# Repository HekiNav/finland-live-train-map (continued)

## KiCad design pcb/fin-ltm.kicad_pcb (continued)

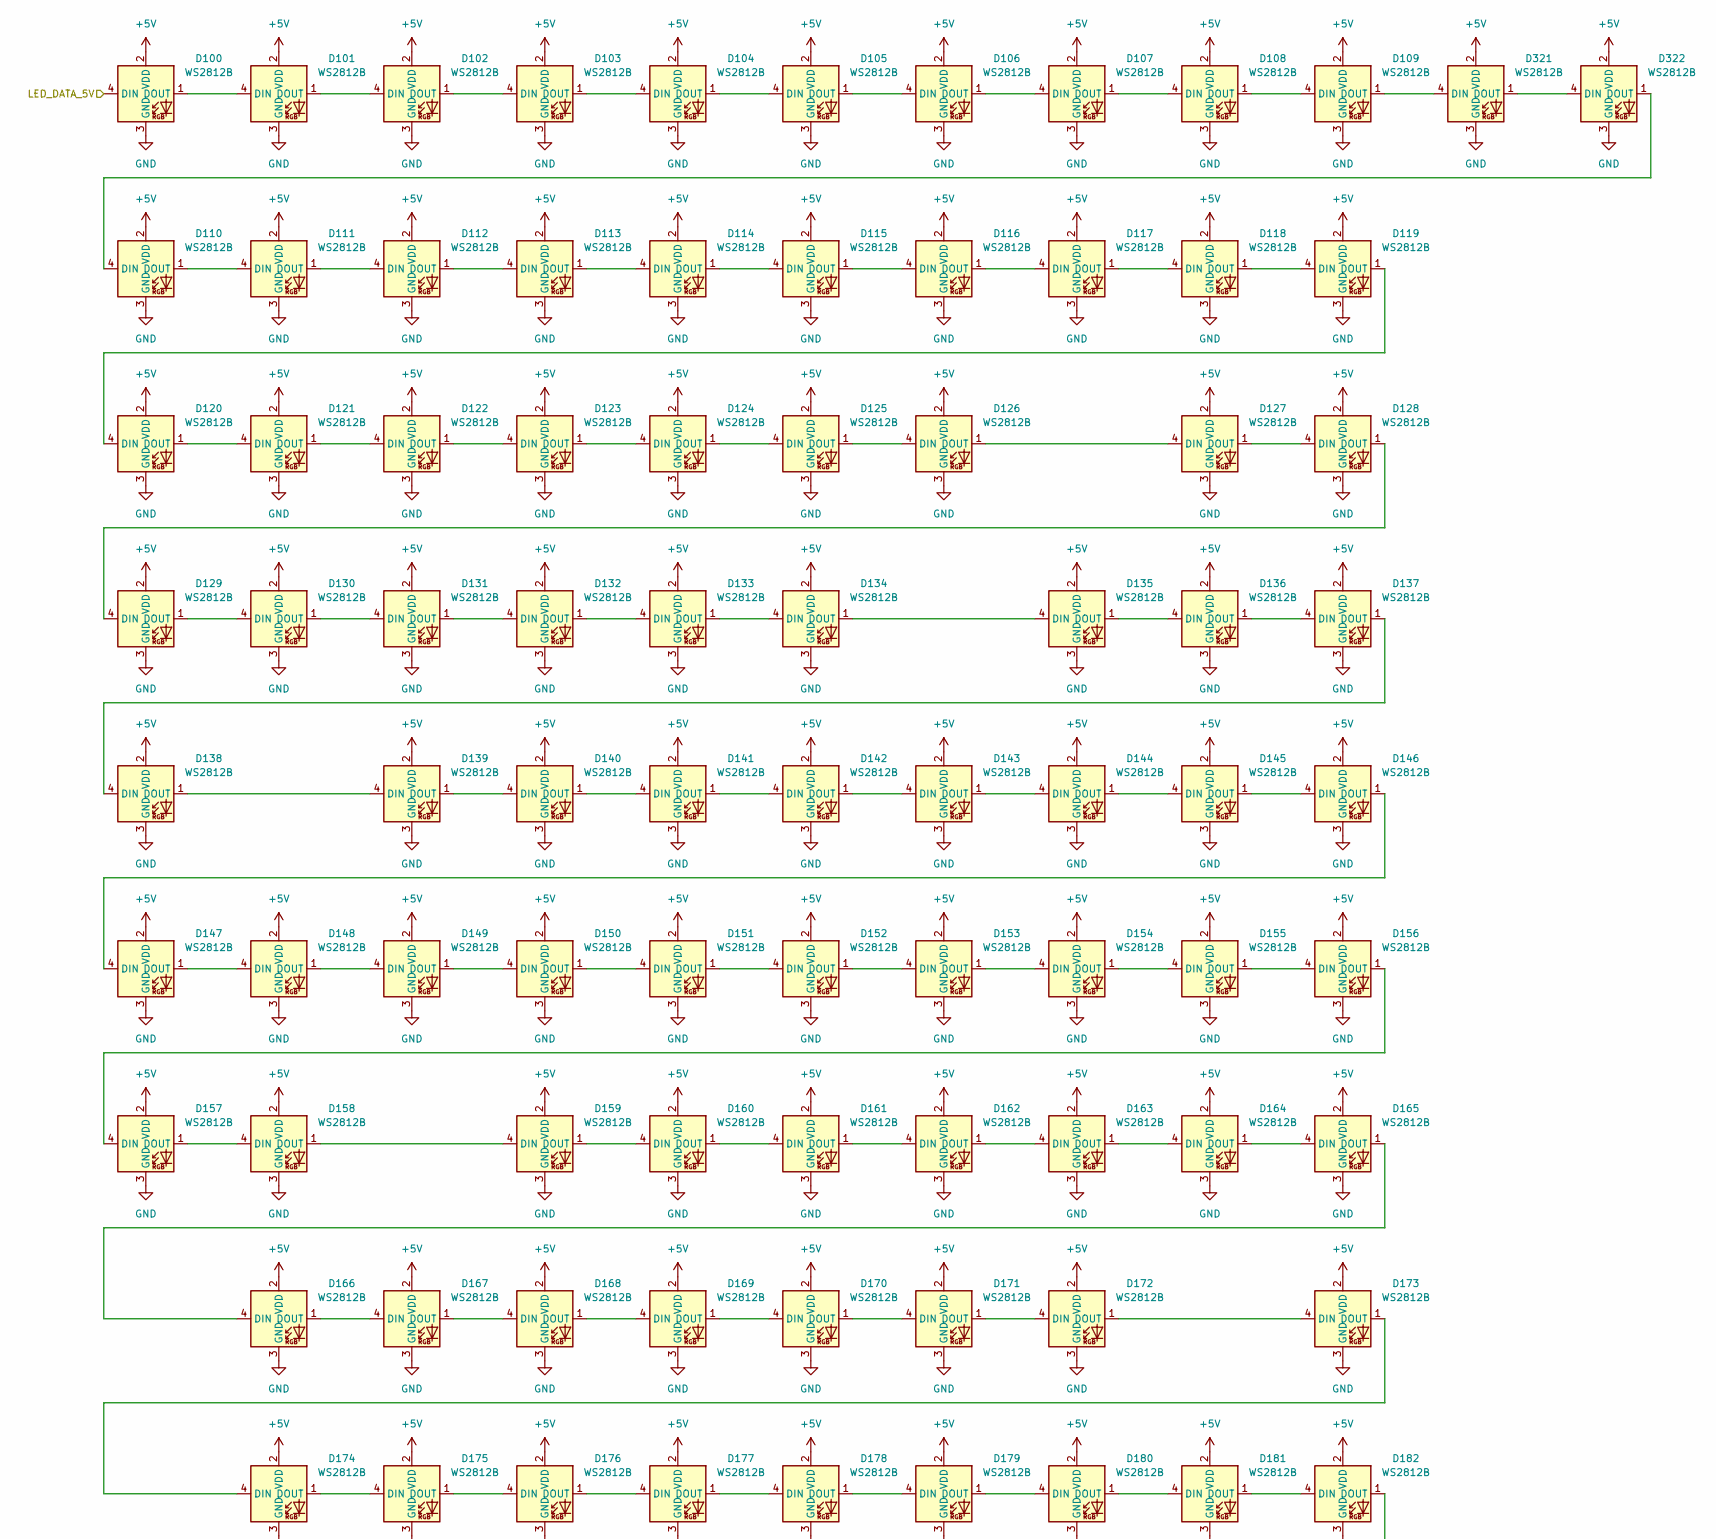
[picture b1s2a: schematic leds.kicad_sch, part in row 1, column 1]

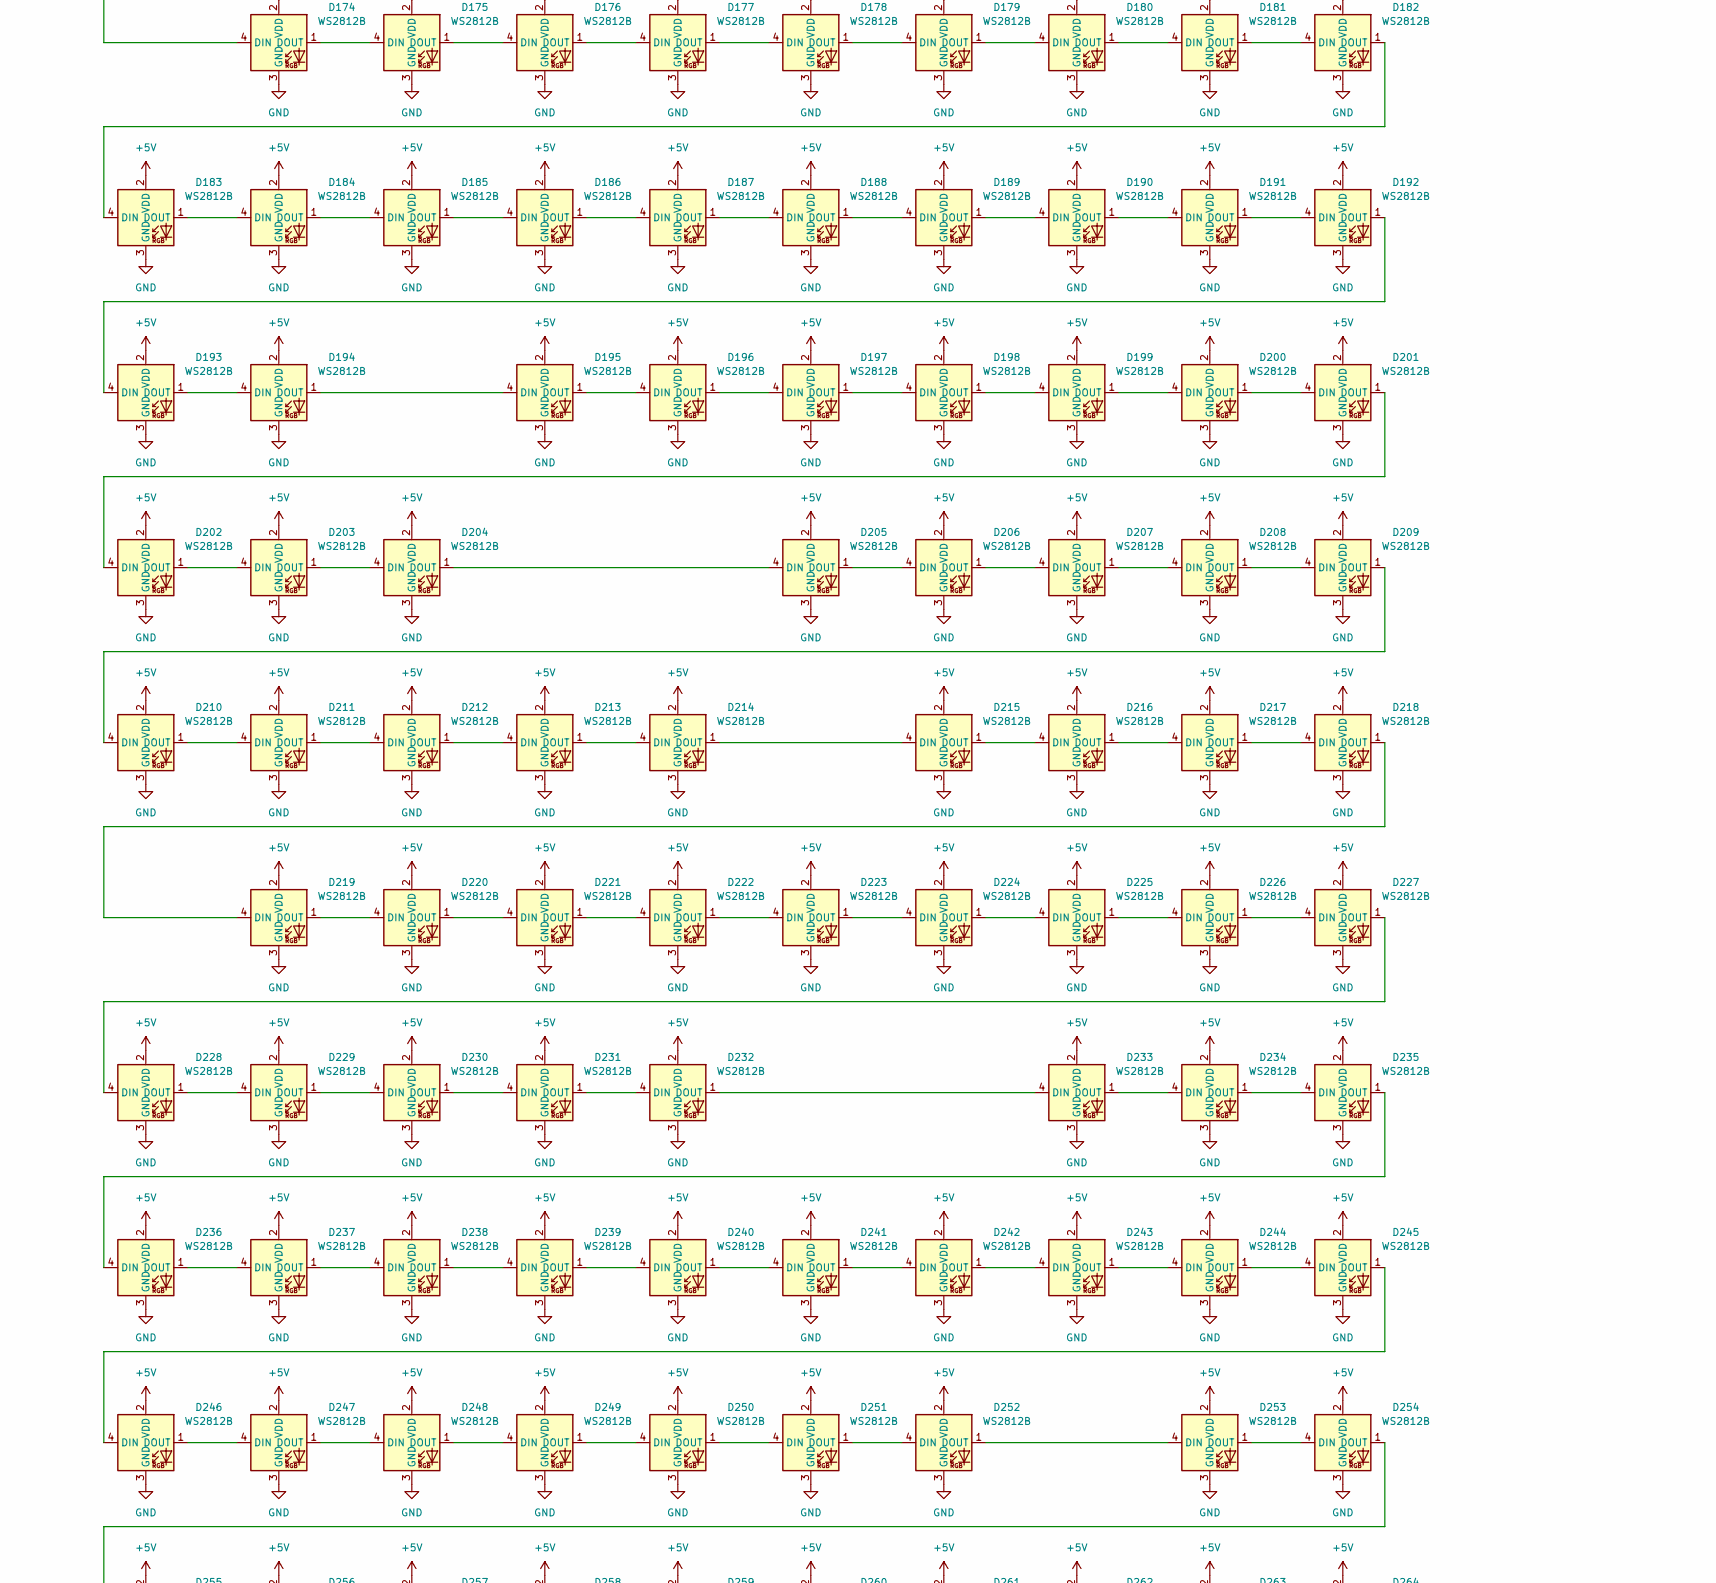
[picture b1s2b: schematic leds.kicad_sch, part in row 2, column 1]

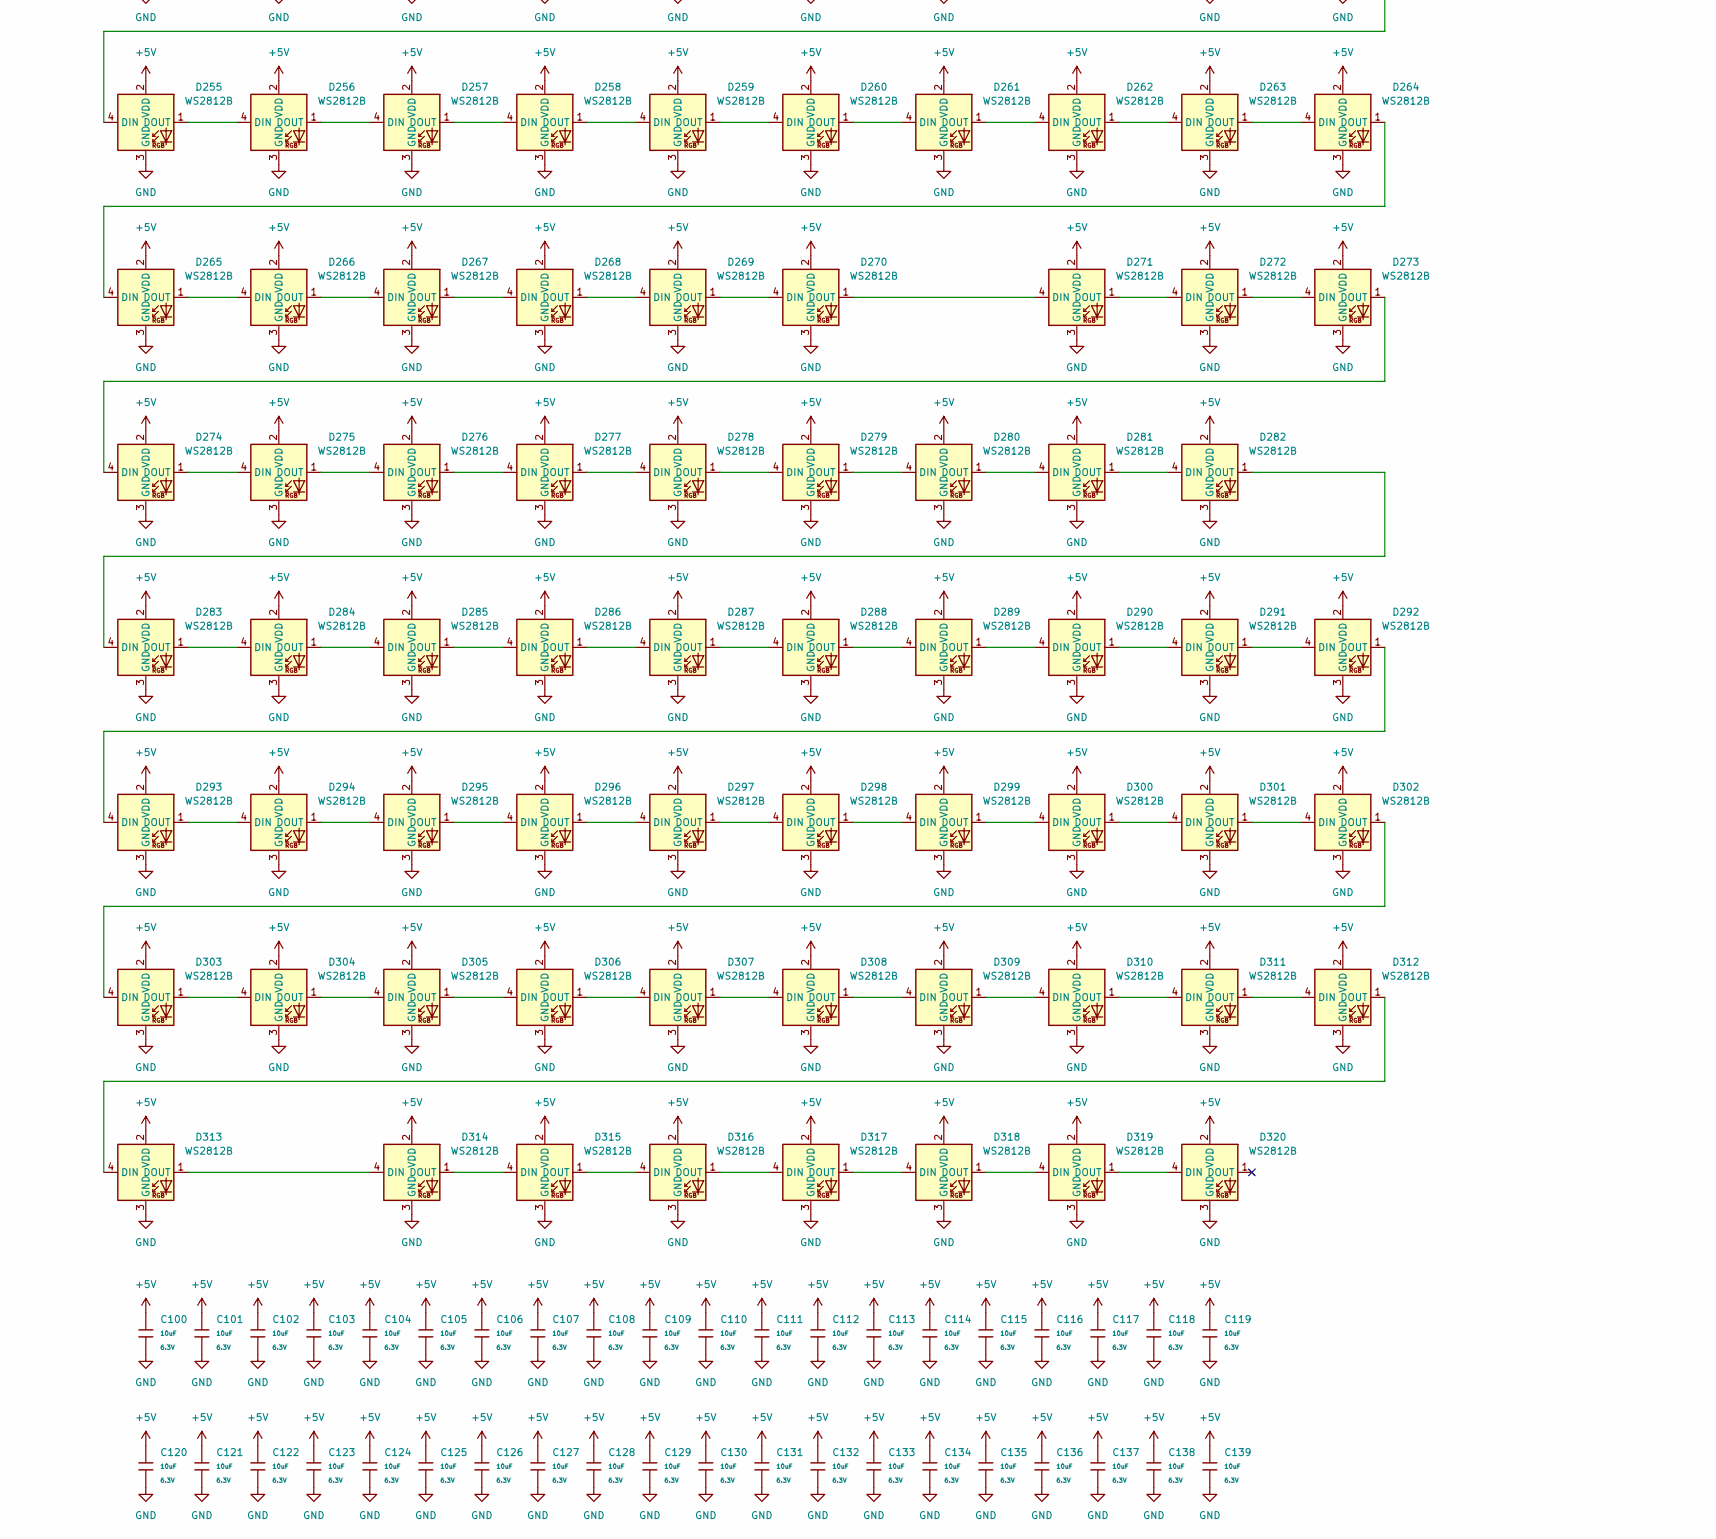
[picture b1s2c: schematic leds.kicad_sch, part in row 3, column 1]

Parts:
C100, C101, C102, C103, C104, C105, C106, C107, C108, C109, C110, C111, C112, C113, C114, C115, C116, C117, C118, C119, C120, C121, C122, C123, C124, C125, C126, C127, C128, C129, C130, C131, C132, C133, C134, C135, C136, C137, C138, C139: 10uF; C_0402; Voltage Rated 6.3V; Tolerance ±20%; Part CL05A106MQ5NUNC; LCSC C15525
D100, D101, D102, D103, D104, D105, D106, D107, D108, D109, D110, D111, D112, D113, D114, D115, D116, D117, D118, D119, D120, D121, D122, D123, D124, D125, D126, D127, D128, D129, D130, D131, D132, D133, D134, D135, D136, D137, D138, D139, D140, D141, D142, D143, D144, D145, D146, D147, D148, D149, D150, D151, D152, D153, D154, D155, D156, D157, D158, D159, D160, D161, D162, D163, D164, D165, D166, D167, D168, D169, D170, D171, D172, D173, D174, D175, D176, D177, D178, D179, D180, D181, D182, D183, D184, D185, D186, D187, D188, D189, D190, D191, D192, D193, D194, D195, D196, D197, D198, D199, D200, D201, D202, D203, D204, D205, D206, D207, D208, D209, D210, D211, D212, D213, D214, D215, D216, D217, D218, D219, D220, D221, D222, D223, D224, D225, D226, D227, D228, D229, D230, D231, D232, D233, D234, D235, D236, D237, D238, D239, D240, D241, D242, D243, D244, D245, D246, D247, D248, D249, D250, D251, D252, D253, D254, D255, D256, D257, D258, D259, D260, D261, D262, D263, D264, D265, D266, D267, D268, D269, D270, D271, D272, D273, D274, D275, D276, D277, D278, D279, D280, D281, D282, D283, D284, D285, D286, D287, D288, D289, D290, D291, D292, D293, D294, D295, D296, D297, D298, D299, D300, D301, D302, D303, D304, D305, D306, D307, D308, D309, D310, D311, D312, D313, D314, D315, D316, D317, D318, D319, D320, D321, D322: WS2812B; LED-SMD_4P-L1.6-W1.5_XL-1615RGBC-WS2812B; LCSC C5349954

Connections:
+5V: C100.1, C101.1, C102.1, C103.1, C104.1, C105.1, C106.1, C107.1, C108.1, C109.1, C110.1, C111.1, C112.1, C113.1, C114.1, C115.1, C116.1, C117.1, C118.1, C119.1, C120.1, C121.1, C122.1, C123.1, C124.1, C125.1, C126.1, C127.1, C128.1, C129.1, C130.1, C131.1, C132.1, C133.1, C134.1, C135.1, C136.1, C137.1, C138.1, C139.1, D100.2 (VDD), D101.2 (VDD), D102.2 (VDD), D103.2 (VDD), D104.2 (VDD), D105.2 (VDD), D106.2 (VDD), D107.2 (VDD), D108.2 (VDD), D109.2 (VDD), D110.2 (VDD), D111.2 (VDD), D112.2 (VDD), D113.2 (VDD), D114.2 (VDD), D115.2 (VDD), D116.2 (VDD), D117.2 (VDD), D118.2 (VDD), D119.2 (VDD), D120.2 (VDD), D121.2 (VDD), D122.2 (VDD), D123.2 (VDD), D124.2 (VDD), D125.2 (VDD), D126.2 (VDD), D127.2 (VDD), D128.2 (VDD), D129.2 (VDD), D130.2 (VDD), D131.2 (VDD), D132.2 (VDD), D133.2 (VDD), D134.2 (VDD), D135.2 (VDD), D136.2 (VDD), D137.2 (VDD), D138.2 (VDD), D139.2 (VDD), D140.2 (VDD), D141.2 (VDD), D142.2 (VDD), D143.2 (VDD), D144.2 (VDD), D145.2 (VDD), D146.2 (VDD), D147.2 (VDD), D148.2 (VDD), D149.2 (VDD), D150.2 (VDD), D151.2 (VDD), D152.2 (VDD), D153.2 (VDD), D154.2 (VDD), D155.2 (VDD), D156.2 (VDD), D157.2 (VDD), D158.2 (VDD), D159.2 (VDD), D160.2 (VDD), D161.2 (VDD), D162.2 (VDD), D163.2 (VDD), D164.2 (VDD), D165.2 (VDD), D166.2 (VDD), D167.2 (VDD), D168.2 (VDD), D169.2 (VDD), D170.2 (VDD), D171.2 (VDD), D172.2 (VDD), D173.2 (VDD), D174.2 (VDD), D175.2 (VDD), D176.2 (VDD), D177.2 (VDD), D178.2 (VDD), D179.2 (VDD), D180.2 (VDD), D181.2 (VDD), D182.2 (VDD), D183.2 (VDD), D184.2 (VDD), D185.2 (VDD), D186.2 (VDD), D187.2 (VDD), D188.2 (VDD), D189.2 (VDD), D190.2 (VDD), D191.2 (VDD), D192.2 (VDD), D193.2 (VDD), D194.2 (VDD), D195.2 (VDD), D196.2 (VDD), D197.2 (VDD), D198.2 (VDD), D199.2 (VDD), D200.2 (VDD), D201.2 (VDD), D202.2 (VDD), D203.2 (VDD), D204.2 (VDD), D205.2 (VDD), D206.2 (VDD), D207.2 (VDD), D208.2 (VDD), D209.2 (VDD), D210.2 (VDD), D211.2 (VDD), D212.2 (VDD), D213.2 (VDD), D214.2 (VDD), D215.2 (VDD), D216.2 (VDD), D217.2 (VDD), D218.2 (VDD), D219.2 (VDD), D220.2 (VDD), D221.2 (VDD), D222.2 (VDD), D223.2 (VDD), D224.2 (VDD), D225.2 (VDD), D226.2 (VDD), D227.2 (VDD), D228.2 (VDD), D229.2 (VDD), D230.2 (VDD), D231.2 (VDD), D232.2 (VDD), D233.2 (VDD), D234.2 (VDD), D235.2 (VDD), D236.2 (VDD), D237.2 (VDD), D238.2 (VDD), D239.2 (VDD), D240.2 (VDD), D241.2 (VDD), D242.2 (VDD), D243.2 (VDD), D244.2 (VDD), D245.2 (VDD), D246.2 (VDD), D247.2 (VDD), D248.2 (VDD), D249.2 (VDD), D250.2 (VDD), D251.2 (VDD), D252.2 (VDD), D253.2 (VDD), D254.2 (VDD), D255.2 (VDD), D256.2 (VDD), D257.2 (VDD), D258.2 (VDD), D259.2 (VDD), D260.2 (VDD), D261.2 (VDD), D262.2 (VDD), D263.2 (VDD), D264.2 (VDD), D265.2 (VDD), D266.2 (VDD), D267.2 (VDD), D268.2 (VDD), D269.2 (VDD), D270.2 (VDD), D271.2 (VDD), D272.2 (VDD), D273.2 (VDD), D274.2 (VDD), D275.2 (VDD), D276.2 (VDD), D277.2 (VDD), D278.2 (VDD), D279.2 (VDD), D280.2 (VDD), D281.2 (VDD), D282.2 (VDD), D283.2 (VDD), D284.2 (VDD), D285.2 (VDD), D286.2 (VDD), D287.2 (VDD), D288.2 (VDD), D289.2 (VDD), D290.2 (VDD), D291.2 (VDD), D292.2 (VDD), D293.2 (VDD), D294.2 (VDD), D295.2 (VDD), D296.2 (VDD), D297.2 (VDD), D298.2 (VDD), D299.2 (VDD), D300.2 (VDD), D301.2 (VDD), D302.2 (VDD), D303.2 (VDD), D304.2 (VDD), D305.2 (VDD), D306.2 (VDD), D307.2 (VDD), D308.2 (VDD), D309.2 (VDD), D310.2 (VDD), D311.2 (VDD), D312.2 (VDD), D313.2 (VDD), D314.2 (VDD), D315.2 (VDD), D316.2 (VDD), D317.2 (VDD), D318.2 (VDD), D319.2 (VDD), D320.2 (VDD), D321.2 (VDD), D322.2 (VDD); also elsewhere on the board
/Leds/LED_DATA_5V: D100.4 (DIN); also elsewhere on the board
GND: C100.2, C101.2, C102.2, C103.2, C104.2, C105.2, C106.2, C107.2, C108.2, C109.2, C110.2, C111.2, C112.2, C113.2, C114.2, C115.2, C116.2, C117.2, C118.2, C119.2, C120.2, C121.2, C122.2, C123.2, C124.2, C125.2, C126.2, C127.2, C128.2, C129.2, C130.2, C131.2, C132.2, C133.2, C134.2, C135.2, C136.2, C137.2, C138.2, C139.2, D100.3 (GND), D101.3 (GND), D102.3 (GND), D103.3 (GND), D104.3 (GND), D105.3 (GND), D106.3 (GND), D107.3 (GND), D108.3 (GND), D109.3 (GND), D110.3 (GND), D111.3 (GND), D112.3 (GND), D113.3 (GND), D114.3 (GND), D115.3 (GND), D116.3 (GND), D117.3 (GND), D118.3 (GND), D119.3 (GND), D120.3 (GND), D121.3 (GND), D122.3 (GND), D123.3 (GND), D124.3 (GND), D125.3 (GND), D126.3 (GND), D127.3 (GND), D128.3 (GND), D129.3 (GND), D130.3 (GND), D131.3 (GND), D132.3 (GND), D133.3 (GND), D134.3 (GND), D135.3 (GND), D136.3 (GND), D137.3 (GND), D138.3 (GND), D139.3 (GND), D140.3 (GND), D141.3 (GND), D142.3 (GND), D143.3 (GND), D144.3 (GND), D145.3 (GND), D146.3 (GND), D147.3 (GND), D148.3 (GND), D149.3 (GND), D150.3 (GND), D151.3 (GND), D152.3 (GND), D153.3 (GND), D154.3 (GND), D155.3 (GND), D156.3 (GND), D157.3 (GND), D158.3 (GND), D159.3 (GND), D160.3 (GND), D161.3 (GND), D162.3 (GND), D163.3 (GND), D164.3 (GND), D165.3 (GND), D166.3 (GND), D167.3 (GND), D168.3 (GND), D169.3 (GND), D170.3 (GND), D171.3 (GND), D172.3 (GND), D173.3 (GND), D174.3 (GND), D175.3 (GND), D176.3 (GND), D177.3 (GND), D178.3 (GND), D179.3 (GND), D180.3 (GND), D181.3 (GND), D182.3 (GND), D183.3 (GND), D184.3 (GND), D185.3 (GND), D186.3 (GND), D187.3 (GND), D188.3 (GND), D189.3 (GND), D190.3 (GND), D191.3 (GND), D192.3 (GND), D193.3 (GND), D194.3 (GND), D195.3 (GND), D196.3 (GND), D197.3 (GND), D198.3 (GND), D199.3 (GND), D200.3 (GND), D201.3 (GND), D202.3 (GND), D203.3 (GND), D204.3 (GND), D205.3 (GND), D206.3 (GND), D207.3 (GND), D208.3 (GND), D209.3 (GND), D210.3 (GND), D211.3 (GND), D212.3 (GND), D213.3 (GND), D214.3 (GND), D215.3 (GND), D216.3 (GND), D217.3 (GND), D218.3 (GND), D219.3 (GND), D220.3 (GND), D221.3 (GND), D222.3 (GND), D223.3 (GND), D224.3 (GND), D225.3 (GND), D226.3 (GND), D227.3 (GND), D228.3 (GND), D229.3 (GND), D230.3 (GND), D231.3 (GND), D232.3 (GND), D233.3 (GND), D234.3 (GND), D235.3 (GND), D236.3 (GND), D237.3 (GND), D238.3 (GND), D239.3 (GND), D240.3 (GND), D241.3 (GND), D242.3 (GND), D243.3 (GND), D244.3 (GND), D245.3 (GND), D246.3 (GND), D247.3 (GND), D248.3 (GND), D249.3 (GND), D250.3 (GND), D251.3 (GND), D252.3 (GND), D253.3 (GND), D254.3 (GND), D255.3 (GND), D256.3 (GND), D257.3 (GND), D258.3 (GND), D259.3 (GND), D260.3 (GND), D261.3 (GND), D262.3 (GND), D263.3 (GND), D264.3 (GND), D265.3 (GND), D266.3 (GND), D267.3 (GND), D268.3 (GND), D269.3 (GND), D270.3 (GND), D271.3 (GND), D272.3 (GND), D273.3 (GND), D274.3 (GND), D275.3 (GND), D276.3 (GND), D277.3 (GND), D278.3 (GND), D279.3 (GND), D280.3 (GND), D281.3 (GND), D282.3 (GND), D283.3 (GND), D284.3 (GND), D285.3 (GND), D286.3 (GND), D287.3 (GND), D288.3 (GND), D289.3 (GND), D290.3 (GND), D291.3 (GND), D292.3 (GND), D293.3 (GND), D294.3 (GND), D295.3 (GND), D296.3 (GND), D297.3 (GND), D298.3 (GND), D299.3 (GND), D300.3 (GND), D301.3 (GND), D302.3 (GND), D303.3 (GND), D304.3 (GND), D305.3 (GND), D306.3 (GND), D307.3 (GND), D308.3 (GND), D309.3 (GND), D310.3 (GND), D311.3 (GND), D312.3 (GND), D313.3 (GND), D314.3 (GND), D315.3 (GND), D316.3 (GND), D317.3 (GND), D318.3 (GND), D319.3 (GND), D320.3 (GND), D321.3 (GND), D322.3 (GND); also elsewhere on the board
unnamed: D100.1 (DOUT), D101.4 (DIN)
unnamed: D101.1 (DOUT), D102.4 (DIN)
unnamed: D102.1 (DOUT), D103.4 (DIN)
unnamed: D103.1 (DOUT), D104.4 (DIN)
unnamed: D104.1 (DOUT), D105.4 (DIN)
unnamed: D105.1 (DOUT), D106.4 (DIN)
unnamed: D106.1 (DOUT), D107.4 (DIN)
unnamed: D107.1 (DOUT), D108.4 (DIN)
unnamed: D108.1 (DOUT), D109.4 (DIN)
unnamed: D109.1 (DOUT), D321.4 (DIN)
unnamed: D110.4 (DIN), D322.1 (DOUT)
unnamed: D110.1 (DOUT), D111.4 (DIN)
unnamed: D111.1 (DOUT), D112.4 (DIN)
unnamed: D112.1 (DOUT), D113.4 (DIN)
unnamed: D113.1 (DOUT), D114.4 (DIN)
unnamed: D114.1 (DOUT), D115.4 (DIN)
unnamed: D115.1 (DOUT), D116.4 (DIN)
unnamed: D116.1 (DOUT), D117.4 (DIN)
unnamed: D117.1 (DOUT), D118.4 (DIN)
unnamed: D118.1 (DOUT), D119.4 (DIN)
unnamed: D119.1 (DOUT), D120.4 (DIN)
unnamed: D120.1 (DOUT), D121.4 (DIN)
unnamed: D121.1 (DOUT), D122.4 (DIN)
unnamed: D122.1 (DOUT), D123.4 (DIN)
unnamed: D123.1 (DOUT), D124.4 (DIN)
unnamed: D124.1 (DOUT), D125.4 (DIN)
unnamed: D125.1 (DOUT), D126.4 (DIN)
unnamed: D126.1 (DOUT), D127.4 (DIN)
unnamed: D127.1 (DOUT), D128.4 (DIN)
unnamed: D128.1 (DOUT), D129.4 (DIN)
unnamed: D129.1 (DOUT), D130.4 (DIN)
unnamed: D130.1 (DOUT), D131.4 (DIN)
unnamed: D131.1 (DOUT), D132.4 (DIN)
unnamed: D132.1 (DOUT), D133.4 (DIN)
unnamed: D133.1 (DOUT), D134.4 (DIN)
unnamed: D134.1 (DOUT), D135.4 (DIN)
unnamed: D135.1 (DOUT), D136.4 (DIN)
unnamed: D136.1 (DOUT), D137.4 (DIN)
unnamed: D137.1 (DOUT), D138.4 (DIN)
unnamed: D138.1 (DOUT), D139.4 (DIN)
unnamed: D139.1 (DOUT), D140.4 (DIN)
unnamed: D140.1 (DOUT), D141.4 (DIN)
unnamed: D141.1 (DOUT), D142.4 (DIN)
unnamed: D142.1 (DOUT), D143.4 (DIN)
unnamed: D143.1 (DOUT), D144.4 (DIN)
unnamed: D144.1 (DOUT), D145.4 (DIN)
unnamed: D145.1 (DOUT), D146.4 (DIN)
unnamed: D146.1 (DOUT), D147.4 (DIN)
unnamed: D147.1 (DOUT), D148.4 (DIN)
unnamed: D148.1 (DOUT), D149.4 (DIN)
unnamed: D149.1 (DOUT), D150.4 (DIN)
unnamed: D150.1 (DOUT), D151.4 (DIN)
unnamed: D151.1 (DOUT), D152.4 (DIN)
unnamed: D152.1 (DOUT), D153.4 (DIN)
unnamed: D153.1 (DOUT), D154.4 (DIN)
unnamed: D154.1 (DOUT), D155.4 (DIN)
unnamed: D155.1 (DOUT), D156.4 (DIN)
unnamed: D156.1 (DOUT), D157.4 (DIN)
unnamed: D157.1 (DOUT), D158.4 (DIN)
unnamed: D158.1 (DOUT), D159.4 (DIN)
unnamed: D159.1 (DOUT), D160.4 (DIN)
unnamed: D160.1 (DOUT), D161.4 (DIN)
unnamed: D161.1 (DOUT), D162.4 (DIN)
unnamed: D162.1 (DOUT), D163.4 (DIN)
unnamed: D163.1 (DOUT), D164.4 (DIN)
unnamed: D164.1 (DOUT), D165.4 (DIN)
unnamed: D165.1 (DOUT), D166.4 (DIN)
unnamed: D166.1 (DOUT), D167.4 (DIN)
unnamed: D167.1 (DOUT), D168.4 (DIN)
unnamed: D168.1 (DOUT), D169.4 (DIN)
unnamed: D169.1 (DOUT), D170.4 (DIN)
unnamed: D170.1 (DOUT), D171.4 (DIN)
unnamed: D171.1 (DOUT), D172.4 (DIN)
unnamed: D172.1 (DOUT), D173.4 (DIN)
unnamed: D173.1 (DOUT), D174.4 (DIN)
unnamed: D174.1 (DOUT), D175.4 (DIN)
unnamed: D175.1 (DOUT), D176.4 (DIN)
unnamed: D176.1 (DOUT), D177.4 (DIN)
unnamed: D177.1 (DOUT), D178.4 (DIN)
unnamed: D178.1 (DOUT), D179.4 (DIN)
unnamed: D179.1 (DOUT), D180.4 (DIN)
unnamed: D180.1 (DOUT), D181.4 (DIN)
unnamed: D181.1 (DOUT), D182.4 (DIN)
unnamed: D182.1 (DOUT), D183.4 (DIN)
unnamed: D183.1 (DOUT), D184.4 (DIN)
unnamed: D184.1 (DOUT), D185.4 (DIN)
unnamed: D185.1 (DOUT), D186.4 (DIN)
unnamed: D186.1 (DOUT), D187.4 (DIN)
unnamed: D187.1 (DOUT), D188.4 (DIN)
unnamed: D188.1 (DOUT), D189.4 (DIN)
unnamed: D189.1 (DOUT), D190.4 (DIN)
unnamed: D190.1 (DOUT), D191.4 (DIN)
unnamed: D191.1 (DOUT), D192.4 (DIN)
unnamed: D192.1 (DOUT), D193.4 (DIN)
unnamed: D193.1 (DOUT), D194.4 (DIN)
unnamed: D194.1 (DOUT), D195.4 (DIN)
unnamed: D195.1 (DOUT), D196.4 (DIN)
unnamed: D196.1 (DOUT), D197.4 (DIN)
unnamed: D197.1 (DOUT), D198.4 (DIN)
unnamed: D198.1 (DOUT), D199.4 (DIN)
unnamed: D199.1 (DOUT), D200.4 (DIN)
unnamed: D200.1 (DOUT), D201.4 (DIN)
unnamed: D201.1 (DOUT), D202.4 (DIN)
unnamed: D202.1 (DOUT), D203.4 (DIN)
unnamed: D203.1 (DOUT), D204.4 (DIN)
unnamed: D204.1 (DOUT), D205.4 (DIN)
unnamed: D205.1 (DOUT), D206.4 (DIN)
unnamed: D206.1 (DOUT), D207.4 (DIN)
unnamed: D207.1 (DOUT), D208.4 (DIN)
unnamed: D208.1 (DOUT), D209.4 (DIN)
unnamed: D209.1 (DOUT), D210.4 (DIN)
unnamed: D210.1 (DOUT), D211.4 (DIN)
unnamed: D211.1 (DOUT), D212.4 (DIN)
unnamed: D212.1 (DOUT), D213.4 (DIN)
unnamed: D213.1 (DOUT), D214.4 (DIN)
unnamed: D214.1 (DOUT), D215.4 (DIN)
unnamed: D215.1 (DOUT), D216.4 (DIN)
unnamed: D216.1 (DOUT), D217.4 (DIN)
unnamed: D217.1 (DOUT), D218.4 (DIN)
unnamed: D218.1 (DOUT), D219.4 (DIN)
unnamed: D219.1 (DOUT), D220.4 (DIN)
unnamed: D220.1 (DOUT), D221.4 (DIN)
unnamed: D221.1 (DOUT), D222.4 (DIN)
unnamed: D222.1 (DOUT), D223.4 (DIN)
unnamed: D223.1 (DOUT), D224.4 (DIN)
unnamed: D224.1 (DOUT), D225.4 (DIN)
unnamed: D225.1 (DOUT), D226.4 (DIN)
unnamed: D226.1 (DOUT), D227.4 (DIN)
unnamed: D227.1 (DOUT), D228.4 (DIN)
unnamed: D228.1 (DOUT), D229.4 (DIN)
unnamed: D229.1 (DOUT), D230.4 (DIN)
unnamed: D230.1 (DOUT), D231.4 (DIN)
unnamed: D231.1 (DOUT), D232.4 (DIN)
unnamed: D232.1 (DOUT), D233.4 (DIN)
unnamed: D233.1 (DOUT), D234.4 (DIN)
unnamed: D234.1 (DOUT), D235.4 (DIN)
unnamed: D235.1 (DOUT), D236.4 (DIN)
unnamed: D236.1 (DOUT), D237.4 (DIN)
unnamed: D237.1 (DOUT), D238.4 (DIN)
unnamed: D238.1 (DOUT), D239.4 (DIN)
unnamed: D239.1 (DOUT), D240.4 (DIN)
unnamed: D240.1 (DOUT), D241.4 (DIN)
unnamed: D241.1 (DOUT), D242.4 (DIN)
unnamed: D242.1 (DOUT), D243.4 (DIN)
unnamed: D243.1 (DOUT), D244.4 (DIN)
unnamed: D244.1 (DOUT), D245.4 (DIN)
unnamed: D245.1 (DOUT), D246.4 (DIN)
unnamed: D246.1 (DOUT), D247.4 (DIN)
unnamed: D247.1 (DOUT), D248.4 (DIN)
unnamed: D248.1 (DOUT), D249.4 (DIN)
unnamed: D249.1 (DOUT), D250.4 (DIN)
unnamed: D250.1 (DOUT), D251.4 (DIN)
unnamed: D251.1 (DOUT), D252.4 (DIN)
unnamed: D252.1 (DOUT), D253.4 (DIN)
unnamed: D253.1 (DOUT), D254.4 (DIN)
unnamed: D254.1 (DOUT), D255.4 (DIN)
unnamed: D255.1 (DOUT), D256.4 (DIN)
unnamed: D256.1 (DOUT), D257.4 (DIN)
unnamed: D257.1 (DOUT), D258.4 (DIN)
unnamed: D258.1 (DOUT), D259.4 (DIN)
unnamed: D259.1 (DOUT), D260.4 (DIN)
unnamed: D260.1 (DOUT), D261.4 (DIN)
unnamed: D261.1 (DOUT), D262.4 (DIN)
unnamed: D262.1 (DOUT), D263.4 (DIN)
unnamed: D263.1 (DOUT), D264.4 (DIN)
unnamed: D264.1 (DOUT), D265.4 (DIN)
unnamed: D265.1 (DOUT), D266.4 (DIN)
unnamed: D266.1 (DOUT), D267.4 (DIN)
unnamed: D267.1 (DOUT), D268.4 (DIN)
unnamed: D268.1 (DOUT), D269.4 (DIN)
unnamed: D269.1 (DOUT), D270.4 (DIN)
unnamed: D270.1 (DOUT), D271.4 (DIN)
unnamed: D271.1 (DOUT), D272.4 (DIN)
unnamed: D272.1 (DOUT), D273.4 (DIN)
unnamed: D273.1 (DOUT), D274.4 (DIN)
unnamed: D274.1 (DOUT), D275.4 (DIN)
unnamed: D275.1 (DOUT), D276.4 (DIN)
unnamed: D276.1 (DOUT), D277.4 (DIN)
unnamed: D277.1 (DOUT), D278.4 (DIN)
unnamed: D278.1 (DOUT), D279.4 (DIN)
unnamed: D279.1 (DOUT), D280.4 (DIN)
unnamed: D280.1 (DOUT), D281.4 (DIN)
unnamed: D281.1 (DOUT), D282.4 (DIN)
unnamed: D282.1 (DOUT), D283.4 (DIN)
unnamed: D283.1 (DOUT), D284.4 (DIN)
unnamed: D284.1 (DOUT), D285.4 (DIN)
unnamed: D285.1 (DOUT), D286.4 (DIN)
unnamed: D286.1 (DOUT), D287.4 (DIN)
unnamed: D287.1 (DOUT), D288.4 (DIN)
unnamed: D288.1 (DOUT), D289.4 (DIN)
unnamed: D289.1 (DOUT), D290.4 (DIN)
unnamed: D290.1 (DOUT), D291.4 (DIN)
unnamed: D291.1 (DOUT), D292.4 (DIN)
unnamed: D292.1 (DOUT), D293.4 (DIN)
unnamed: D293.1 (DOUT), D294.4 (DIN)
unnamed: D294.1 (DOUT), D295.4 (DIN)
unnamed: D295.1 (DOUT), D296.4 (DIN)
unnamed: D296.1 (DOUT), D297.4 (DIN)
unnamed: D297.1 (DOUT), D298.4 (DIN)
unnamed: D298.1 (DOUT), D299.4 (DIN)
unnamed: D299.1 (DOUT), D300.4 (DIN)
unnamed: D300.1 (DOUT), D301.4 (DIN)
unnamed: D301.1 (DOUT), D302.4 (DIN)
unnamed: D302.1 (DOUT), D303.4 (DIN)
unnamed: D303.1 (DOUT), D304.4 (DIN)
unnamed: D304.1 (DOUT), D305.4 (DIN)
unnamed: D305.1 (DOUT), D306.4 (DIN)
unnamed: D306.1 (DOUT), D307.4 (DIN)
unnamed: D307.1 (DOUT), D308.4 (DIN)
unnamed: D308.1 (DOUT), D309.4 (DIN)
unnamed: D309.1 (DOUT), D310.4 (DIN)
unnamed: D310.1 (DOUT), D311.4 (DIN)
unnamed: D311.1 (DOUT), D312.4 (DIN)
unnamed: D312.1 (DOUT), D313.4 (DIN)
unnamed: D313.1 (DOUT), D314.4 (DIN)
unnamed: D314.1 (DOUT), D315.4 (DIN)
unnamed: D315.1 (DOUT), D316.4 (DIN)
unnamed: D316.1 (DOUT), D317.4 (DIN)
unnamed: D317.1 (DOUT), D318.4 (DIN)
unnamed: D318.1 (DOUT), D319.4 (DIN)
unnamed: D319.1 (DOUT), D320.4 (DIN)
unnamed: D321.1 (DOUT), D322.4 (DIN)

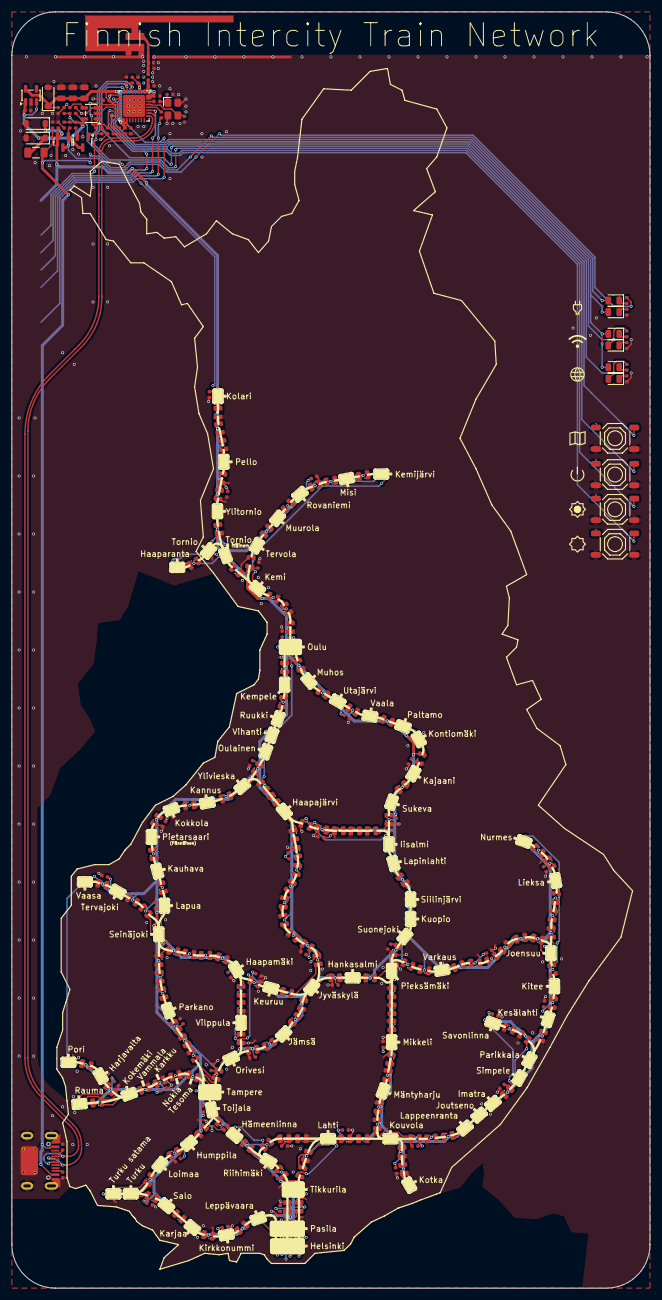
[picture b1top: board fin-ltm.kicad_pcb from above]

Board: 2 copper layers, 110.0 x 220.0 mm, 327 parts (0 on the bottom side), 259 nets.

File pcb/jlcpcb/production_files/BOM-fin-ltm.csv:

Comment,Designator,Footprint,LCSC,Quantity
1.5pF,"C18,C19",C_0402,C1552,2
100kΩ,"R1,R13,R16,R17,R9",R_0402,C25741,5
10kΩ,"R11,R14,R15,R2,R4,R5",R_0402,C25744,6
10uF,"C1,C10,C100,C101,C102,C103,C104,C105,C106,C107,C108,C109,C11,C110,C111,C112,C113,C114,C115,C116,C117,C118,C119,C12,C120,C121,C122,C123,C124,C125,C126,C127,C128,C129,C13,C130,C131,C132,C133,C134,C135,C136,C137,C138,C139,C14,C15,C2,C20,C21,C3,C4,C5,C6",C_0402,C15525,54
"15nH,300mA",L1,L_0402,C27143,1
2.7nH,L2,L_0402,C77108,1
27pF,"C16,C17",C_0402,C1557,2
"40MHz, 15pF",X1,OSC-SMD_4P-L3.2-W2.5-BL_SIT8008BI,C9010,1
47uF,"C7,C8,C9",C_0805,C16780,3
5.1kΩ,"R3,R6,R7",R_0402,C25905,3
510kΩ,"R10,R12",R_0402,C11616,2
510Ω,R8,R_0402,C25123,1
"Connector, USB-TYPE-C-16P",J1,TYPE-C-SMD_HX-TYPE-C-16PIN,C2927039,1
ESP32-C3FH4,U2,QFN-32-1EP_5x5mm_P0.5mm_EP3.7x3.7mm_ThermalVias,C2858491,1
Green,"D1,D10,D9",D_0805,C2297,3
H3V3U10B,D6,D_DFN1006-2L,C20615782,1
HL3415A,Q1,Q_SOT-23,C28646270,1
MM1W5V6,"D4,D5",D_SOD-123,C22435086,2
MMBT3904,Q2,Q_SOT-23,C7420353,1
MMSZ5227B,D3,D_SOD-123,C22395553,1
"Polyfuse, 2A",F1,Fuse_1206_3216Metric,C6165195,1
Red,"D2,D7,D8",D_0805,C84256,3
SN74LV1T34DBV,U3,SOT-23-5,C100024,1
"Tactile Button, 160gf","S1,S2,S3,S4",SW-SMD_4P-L5.1-W5.1-P3.70-LS6.5-TL-2,C318884,4
WS2812B,"D100,D101,D102,D103,D104,D105,D106,D107,D108,D109,D110,D111,D112,D113,D114,D115,D116,D117,D118,D119,D120,D121,D122,D123,D124,D125,D126,D127,D128,D129,D130,D131,D132,D133,D134,D135,D136,D137,D138,D139,D140,D141,D142,D143,D144,D145,D146,D147,D148,D149,D150,D151,D152,D153,D154,D155,D156,D157,D158,D159,D160,D161,D162,D163,D164,D165,D166,D167,D168,D169,D170,D171,D172,D173,D174,D175,D176,D177,D178,D179,D180,D181,D182,D183,D184,D185,D186,D187,D188,D189,D190,D191,D192,D193,D194,D195,D196,D197,D198,D199,D200,D201,D202,D203,D204,D205,D206,D207,D208,D209,D210,D211,D212,D213,D214,D215,D216,D217,D218,D219,D220,D221,D222,D223,D224,D225,D226,D227,D228,D229,D230,D231,D232,D233,D234,D235,D236,D237,D238,D239,D240,D241,D242,D243,D244,D245,D246,D247,D248,D249,D250,D251,D252,D253,D254,D255,D256,D257,D258,D259,D260,D261,D262,D263,D264,D265,D266,D267,D268,D269,D270,D271,D272,D273,D274,D275,D276,D277,D278,D279,D280,D281,D282,D283,D284,D285,D286,D287,D288,D289,D290,D291,D292,D293,D294,D295,D296,D297,D298,D299,D300,D301,D302,D303,D304,D305,D306,D307,D308,D309,D310,D311,D312,D313,D314,D315,D316,D317,D318,D319,D320,D321,D322",LED-SMD_4P-L1.6-W1.5_XL-1615RGBC-WS2812B,C5349954,223
Antenna_Shield,AE1,Inverted_F_Antenna_2.4Ghz_1.0mmPCB_TI_CC2430DB.pretty,,1
RT9080,U1,TSOT-23-5,,1

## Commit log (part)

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2026-04-19 init
2026-04-19 components researched
2026-04-19 initialized kicad project and started drawing schematic
2026-04-19 Added Geographic map and added stuff to README
2026-04-19 More schematic power system work
2026-04-20 continued schematic
2026-04-20 Fixed ERC issues
2026-04-21 schematic update
2026-04-21 MD update
2026-04-21 Added the improved GeographicalMap and changed README
2026-04-21 Changed formatting of the README
2026-04-22 BOM check and small tweaks
2026-04-27 readme update
2026-04-30 Added geographicalMap without background.
    - Added geographicalMap without background and with a few forgotten lines
2026-04-30 Included signal maps
2026-04-30 server init
2026-04-30 created new data line configuration
2026-04-30 Started adding leds and started making pcbs.
2026-04-30 server updates and battling with kicad
2026-05-03 pcb designed antenna
2026-05-04 pcb update and planning in svg
2026-05-04 design readme update
2026-05-04 more pcb routing
2026-05-04 even more pcb routing
2026-05-05 pcb 2
2026-05-05 pcb 3
2026-05-07 pcb tweaks
2026-05-08 add oled
2026-05-08 led routing
2026-05-08 finished pcb routing
2026-05-08 readme link fix
2026-05-10 server update
2026-05-28 overhauled pcb layout
2026-05-28 Changing the silkscreen and changing led layout
2026-05-28 gitignore update
2026-05-31 smol tweak
2026-06-01 tweaked layout
2026-06-01 smaller tweaks
2026-06-02 finished led placement
2026-06-02 moved usb traces
2026-06-03 pcb mostly done
2026-06-04 linking leds to stations
2026-06-04 kicad something??
2026-06-06 Updated README with more info.
2026-06-06 Changed pcb and exported 3d files
2026-06-07 added led decoupling caps
2026-06-07 readme and server update
2026-06-08 Changed spot of 3d files.
2026-06-08 pcb finished
2026-06-08 remove fill from zones
2026-06-08 readded fill
2026-06-08 added icons to pcb
2026-06-09 readme and pcb fixes
2026-06-09 readme links test
2026-06-09 maybe the links wokr now
2026-06-09 another link test because these only work in gh
2026-06-09 links
2026-06-09 pcb update
2026-06-09 wrote more definitions
2026-06-10 finished linking
2026-06-11 update server
2026-06-11 something pcb idk
2026-06-11 servering
2026-06-15 server done for now
2026-06-15 there is something wrong
2026-06-16 added haaparanta
2026-06-16 oops is forgot these
2026-06-17 finished pcb
2026-06-17 implementing multibetween handling
2026-06-17 Add 3D files for wall mount.
2026-06-17 Add build guide and 3d files README
2026-06-19 updating hki-ltm to the new data format
2026-06-21 copied over the firmware
2026-06-22 firmware update
2026-06-22 trying to fix
2026-06-22 bug fixies
2026-06-22 fixed multibetween handling
2026-06-22 server
2026-06-22 trying to get websockets to work
2026-06-23 firmware websocket fix and server updates
2026-06-23 server fixes
2026-06-23 another fix
2026-06-23 firmware fixes
2026-06-23 firmware and server fixies
2026-06-23 idek atp
2026-06-23 idk something
2026-06-23 fixies (its working now)
2026-06-24 firmware updating
2026-06-24 capcitor fix
2026-06-24 3d files update
2026-06-25 Add jlcpcb manufacturing files.
2026-06-25 Add PCB order instructions
2026-06-25 Update different readme's
2026-06-25 fixed conflivt
2026-06-25 fixing git issues
2026-06-25 testing web installer
2026-06-25 actions test
2026-06-25 mergebin update
2026-06-25 fix build_installer
2026-06-27 update firmware
2026-06-27 fix web installer
2026-06-27 fixed now
2026-06-30 moved software to new repo
2026-06-30 Add MIT License to the project
